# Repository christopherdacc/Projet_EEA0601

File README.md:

# Projet_EEA0601 (Partie IHM)

Programmation en langage C sur MPLAB X IDE d'un microcontrôleur (dsPIC30F4012) pour un système d'IHM d'un robot.
Ce robot a pour fonction de suivre une trajectoire (suit une ligne dessinée par terre), détecter les obstacles et changer de direction pour poursuivre son chemin et une interface IHM pour pouvoir entrer des informations au microcontrôleur avec 3 boutons.

"Séances de travail surveillées et supplémentaires avec tâches réalisées"

* Séance 1 (24/01/2024):
      Explication du projet par les professeurs.
  
* Séance 2 (31/01/2024):
      Branchement d'un afficheur LCD (EA DOGM163W-A) et allumage du rétroéclairage.

* Séance 2.1 sup (02/02/2024):
      programmation et affichage de 'Bonjour le monde!' sur l'écran LCD.
  
* Séance 3 (07/02/2024):
      Branchement des boutons avec leurs résistances spécifiques.

* Séance 4 (14/02/2024):
      Programmation des boutons pour savoir s'ils sont appuyés ou non en affichant leurs états sur l'écran LCD.

* Séance 5 (21/02/2024):
      Rajout des librairies sur Eagle.
      Réalisation du schéma de la carte électronique sur Eagle.

* Séance 5.1 sup (22/02/2024):
      Finalisation du schéma de la carte électronique sur Eagle.
      Début de la réalisation de la carte électronique sur Eagle ainsi que le typon.
* Séance 5.2 sup (23/02/2024):
      Début de la programmation d'un menu avec les options de test des boutons et changement de l'éclairage de l'écran.

* Travail Vacances 6 (du 24/02/2024 au 02/03/2024):
      Finalisation du code menu (prototype)
      Erreur de Build du code.

* Séance 6.1 test du code (05/03/2024):
      Test du code et correction du build error.
      Nouveau probleme code ne marche pas comme on veux.

* Séance 7 (06/03/2024):
      Correction du Schéma de la carte.
      Correction de la carte par rapport au changements du schéma.
      Un peut de modification du code pour qu'il marche (ne marche toujours pas).

* Séance 7.1 sup (07/03/2024):
      Correction de l'affichage du menu (sélection de choix marche bien mais les choix ne marchent pas a 100%)

* Séance 7.2 sup (11/03/2024):
      Correction de la fonction délai.
      Travail sur le compte rendu.

* Séance 8 (13/03/2024):
      On a continué le routage des pistes.
      On a changer les pates des boutons et de l'ecran pour mettre les pates des boutons sur les pates CN qui permettent les interuptions sur front.
  
* Séance 9 (20/03/2024):
      On a finit la carte électronique avec le dimentionnement des pistes de +5V (0.05 inch) et pistes de signaux (0.024).
      On a cassé les angles et tout ca pour evité le rayonnement electromagnetique.

* Séance 10 (27/03/2024):
      On a percé la carte pour pouvoir souder les composants decu.

* Séance 10.1 sup (28/03/2024):
      On a réalisé le test de continuité a l'ohm mètre.
      On a resouder une piste défectueuse.
      On a souder tout les composants sur la carte.
* Séance 11 (03/04/2024):
      Reprogrammation du test des boutons en utilisant des iterruptions.
      Interruptions fonctionnent mais que sur le bouton 3.

* Séance 11.1 sup (09/04/2024):
      Correction du code de l'interruption (Fonctionnement parfait des boutons).
      Essai d'integrer la structure Keyboard avec les objets, mais pas de success.
      Changement du bouton rouge.
      Pendant le test du code, on a rencontrer un probleme de fonctionnement du microcontrolleur.
      Probleme de cablage au niveau de l'alimentation du microcontrolleur.

* Séance 12 (10/04/2024):
      Réglage du probleme de cablage au niveau de l'alimentation du microcontrolleur.
      Le code fonctionne a nouveau.
      Ajout de la fonction menu_principale() pour afficher le menu avec les different choix.
      Programmation de la navigation du curseur pour selectionner 1 des 3 choix avec prog de la saisier du choix 1 (Actions).
* Pour la prochaine séance :        - Essayer de remplacer les statusB, statusN et statusR par la structure keyboard.
                                    - Implémanter cette structure dans la fonction menu_principale().
                                    - Continuer la programmation de l'affichage.
  
* Séance 12.1 sup (13/04/2024):
      On a realiser les taches pécedantes (remplacement statusB.../implementer la struct keyboard.../ continuer la programmation de l'affichage).
      On a essayer d'implémenter les strcutures Menu, MenuItem et MenuValue mais on a pas réussi.

* Séance 12.2 sup (16/04/2024):
      On a continuer l'affichage du menu et differente options du menu avec des if et else if.
      On a réessayer d'implenter les structures Menu, MenuItem et MenuValue maus on a toujours pas réussi.
      On a essayer d'ajouter le keybord->upstate=2 pour une appuie de 2s sur le bouton rouger, mais on a pas réussi.

* To do: try using macros to simplify and reduce memory usage.

* Séance 13 (17/04/2024):
      On a utiliser macros (#define) pour l'operation moyenne%3
      On pu utiliser ticks.c pour pouvoir determiner l'appui de 2s sur un bouton.
      On a continuer la partie parametres->reglage detection obs pour essayer d'afficher un chiffre et l'incrémenter mais l'addition de chiffre et considere comme un char.
      On a vite fait compris le fonctionnement des differentes struct du menu(Menu, MenuItem et MenuValue) et l'utilisation d'une array pour stocker les differents MenuItems.

* To do: implementer les 3 structures du menu a la fonction menu_principale, réessayer la configuration de l'affichage d'un int modifiable sur l'ecran,

* Séance 13.1 sup (19/04/2024):
      On a réussi a configurer l'affichage d'un int qu'on peut incrémenter et décrémenter a l'aide des boutons pour la partie Parametres->Detection obstacle.
  
* Séance 14 (07/05/2024):
      On a finaliser le menu (partie affichage et manupulation du menu).
      Il nous reste la partie parametre (PID et vitesse) a réglé.
      Il nous reste les interruption pour recevoir et transmettre les info des capteurs et moteurs.
      il nous reste a configurer la structure MenuValues pour pouvoir envoyer les parametres au moteur.

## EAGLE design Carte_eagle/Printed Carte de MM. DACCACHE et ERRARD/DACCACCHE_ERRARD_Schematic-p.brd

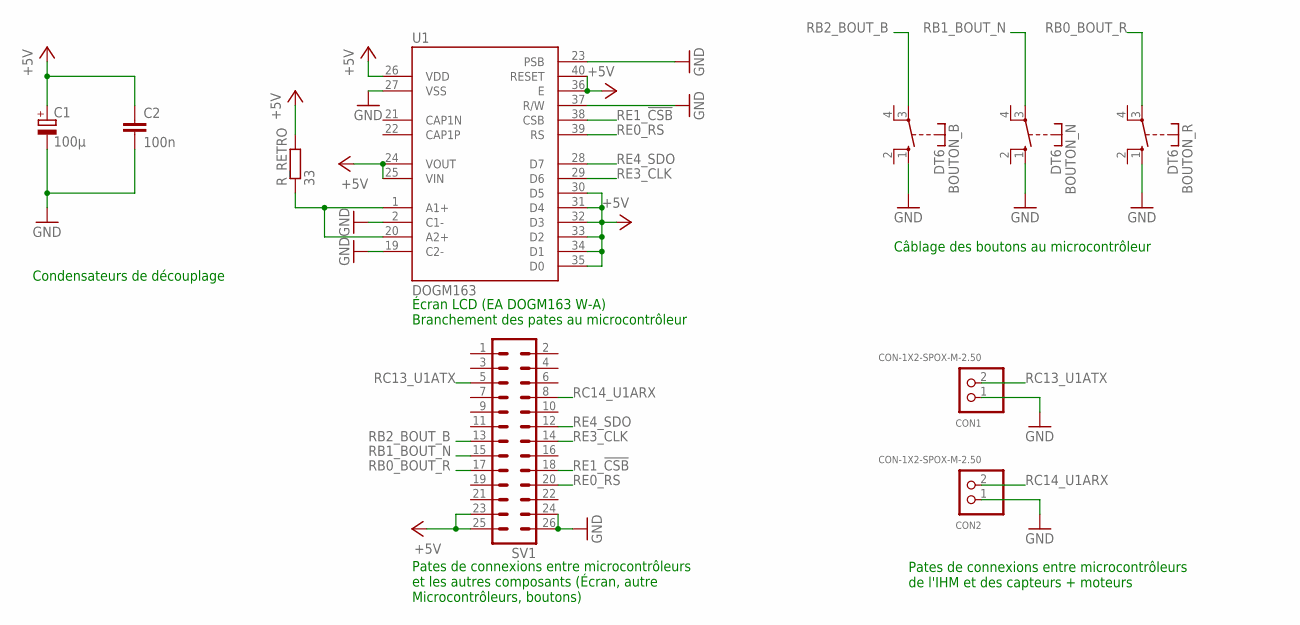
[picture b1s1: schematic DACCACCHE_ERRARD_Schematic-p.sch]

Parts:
BOUTON_B: DT6
BOUTON_N: DT6
BOUTON_R: DT6
C1: 100µ; E2,5-7
C2: 100n; C050-030X075
CON1, CON2: CON-1X2-SPOX-M-2.50; SPOX-M-2.50-02
R_RETRO: 33; 0207/10
SV1: ML26
U1: DOGM163; DOGM

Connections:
+5V: C1.+, C2.1, R_RETRO.2, SV1.23, SV1.25, U1.24 (VOUT), U1.25 (VIN), U1.26 (VDD), U1.30 (D5), U1.31 (D4), U1.32 (D3), U1.33 (D2), U1.34 (D1), U1.35 (D0), U1.36 (E), U1.40 (RESET)
GND: BOUTON_B.1 (S), BOUTON_N.1 (S), BOUTON_R.1 (S), C1.-, C2.2, CON1.1, CON2.1, SV1.24, SV1.26, U1.2 (C1-), U1.19 (C2-), U1.23 (PSB), U1.27 (VSS), U1.37 (R/W)
RB0_BOUT_R: BOUTON_R.3, SV1.17
RB1_BOUT_N: BOUTON_N.3, SV1.15
RB2_BOUT_B: BOUTON_B.3, SV1.13
RC13_U1ATX: CON1.2, SV1.5
RC14_U1ARX: CON2.2, SV1.8
RE0_RS: SV1.20, U1.39 (RS)
RE1_!CSB: SV1.18, U1.38 (CSB)
RE3_CLK: SV1.14, U1.29 (D6)
RE4_SDO: SV1.12, U1.28 (D7)
RHETRO_RES: R_RETRO.1, U1.1 (A1+), U1.20 (A2+)

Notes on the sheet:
Écran LCD (EA DOGM163 W-A) Branchement des pates au microcontrôleur
Câblage des boutons au microcontrôleur
Pates de connexions entre microcontrôleurs de l'IHM et des capteurs + moteurs
Pates de connexions entre microcontrôleurs et les autres composants (Écran, autre Microcontrôleurs, boutons)
Condensateurs de découplage

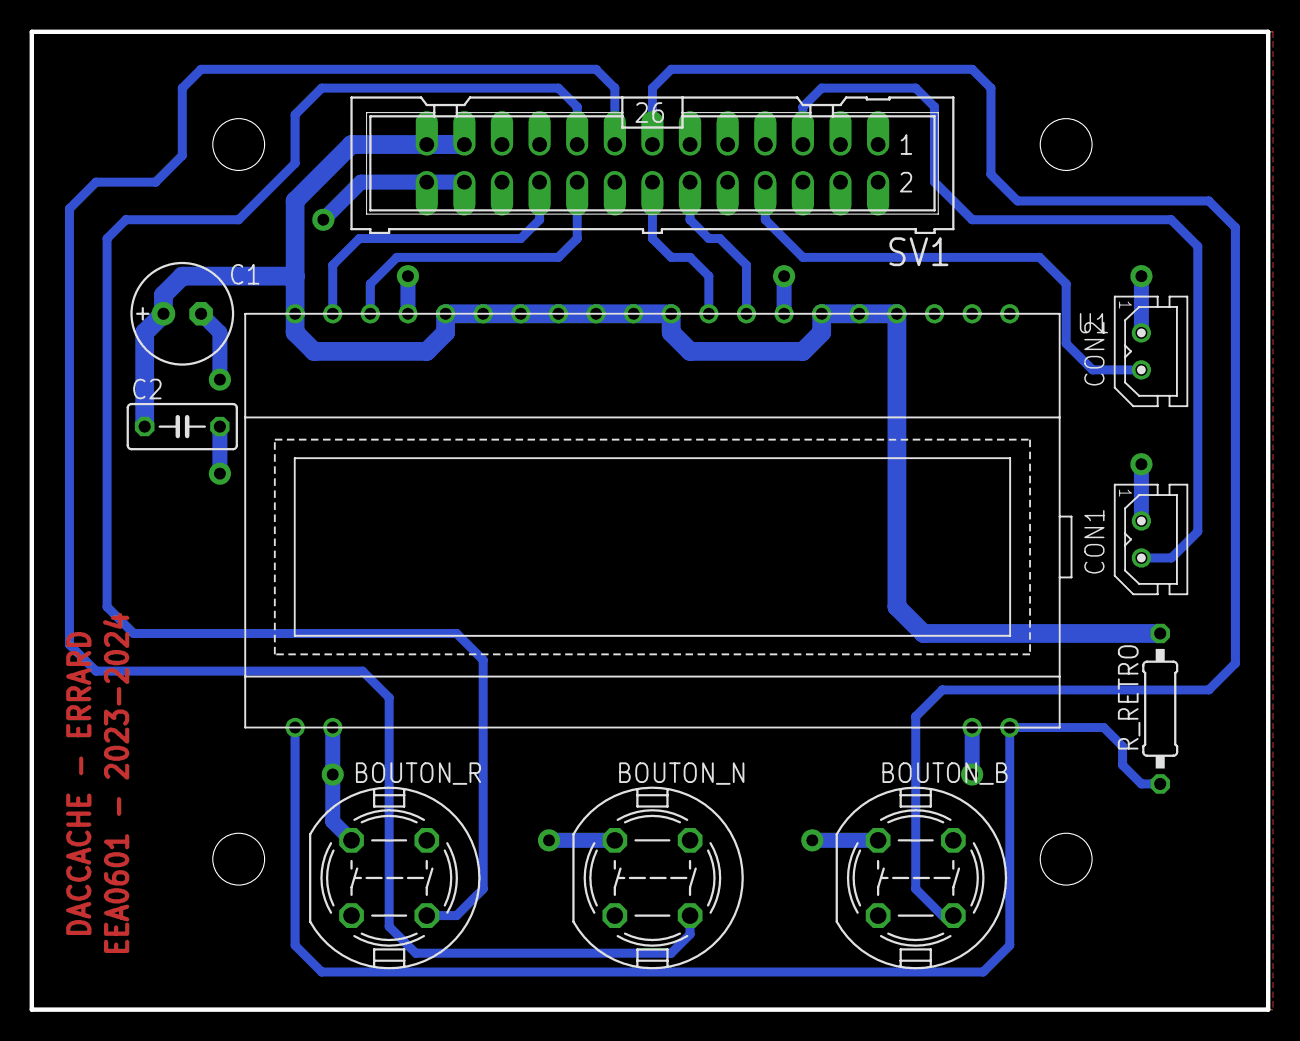
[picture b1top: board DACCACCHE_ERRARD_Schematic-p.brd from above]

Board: 2 copper layers, 83.5 x 66.0 mm, 10 parts (0 on the bottom side), 12 nets.

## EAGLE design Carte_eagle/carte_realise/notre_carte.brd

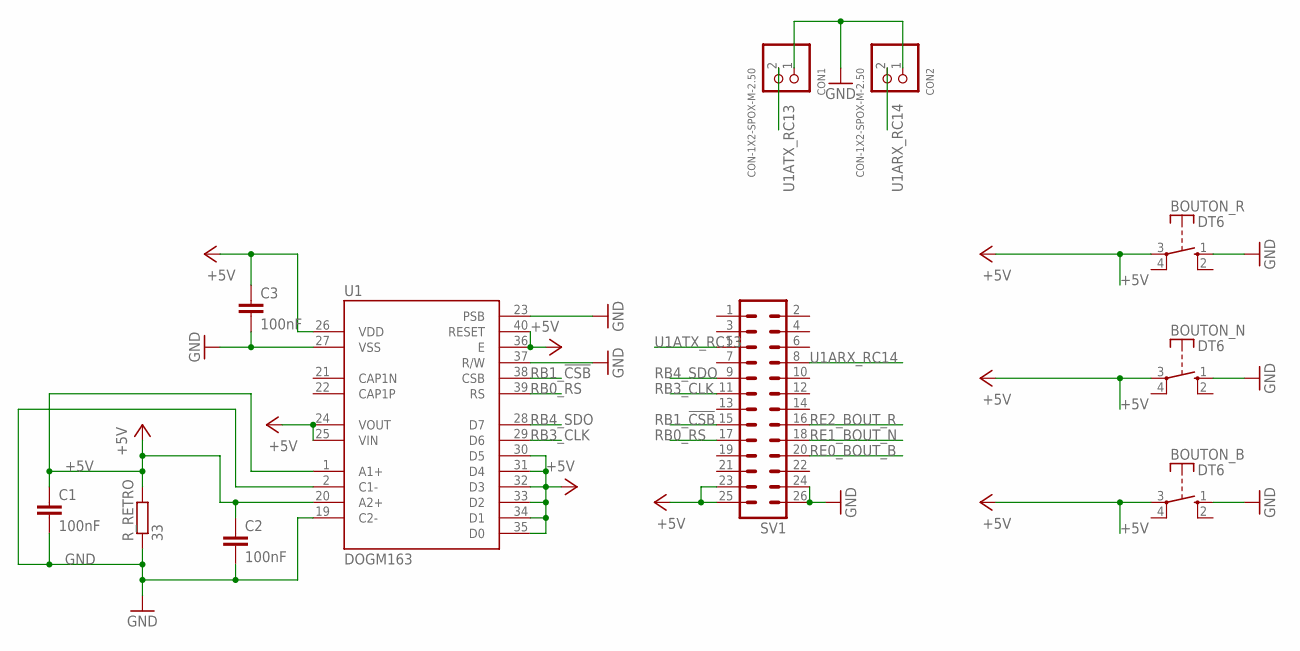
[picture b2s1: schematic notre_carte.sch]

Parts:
BOUTON_B: DT6
BOUTON_N: DT6
BOUTON_R: DT6
C1, C2, C3: 100nF; C025-025X050
CON1, CON2: CON-1X2-SPOX-M-2.50; SPOX-M-2.50-02
R_RETRO: 33; 0207/15
SV1: ML26
U1: DOGM163; DOGM

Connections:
+5V: BOUTON_B.3, BOUTON_N.3, BOUTON_R.3, C1.1, C2.1, C3.1, R_RETRO.2, SV1.23, SV1.25, U1.1 (A1+), U1.20 (A2+), U1.24 (VOUT), U1.25 (VIN), U1.26 (VDD), U1.30 (D5), U1.31 (D4), U1.32 (D3), U1.33 (D2), U1.34 (D1), U1.35 (D0), U1.36 (E), U1.40 (RESET)
GND: BOUTON_B.1 (S), BOUTON_N.1 (S), BOUTON_R.1 (S), C1.2, C2.2, C3.2, CON1.1, CON2.1, R_RETRO.1, SV1.24, SV1.26, U1.2 (C1-), U1.19 (C2-), U1.23 (PSB), U1.27 (VSS), U1.37 (R/W)
RB0_RS: SV1.17, U1.39 (RS)
RB1_!CSB: SV1.15, U1.38 (CSB)
RB3_CLK: SV1.11, U1.29 (D6)
RB4_SDO: SV1.9, U1.28 (D7)
RE0_BOUT_B: SV1.20
RE1_BOUT_N: SV1.18
RE2_BOUT_R: SV1.16
U1ARX_RC14: CON2.2, SV1.8
U1ATX_RC13: CON1.2, SV1.5

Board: 2 copper layers, 11 parts (0 on the bottom side), 8 nets, no tracks yet.

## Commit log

2024-02-21 Create README.md
    Add a new README.md file
2024-02-21 Update README.md
    Update README.md
2024-02-21 Upload Eagle Schematics
    Upload of first eagle schematics: lcd connections, buttons, microcontroller conections using 26 pins connector ML26, pins for other microcontroller connections.
2024-02-21 Upload of Schematics Screenshot
2024-02-21 Update carte elec
2024-02-22 Updated schematics of the board
    mise a jour du schéma de la carte électronique réalisé sur eagle, (addition des capacités de découplage de 100nF et amélioration des connections de fils)
2024-02-22 Delete Carte_eagle/carte_realise/carte_realise directory
    faute d'addition
2024-02-23 Programming changes
    Adding menu function
2024-02-26 Update README.md
    update séance du vendredi 23
2024-03-01 mise a jour du code main.c
    finalisation de la fonction menu dans les fichiers a rajouter apres (fonctions_sup.h et fonctions_sup.c)
2024-03-01 Mise a jour de fonctions_sup.h et fonctions_sup.c
    Finalisation de la fonction du menu (prototype) a essayer en classe
2024-03-06 Update file main.c
    Mise du code dans le fichié fonctions_sup.c
2024-03-06 Modification de fonctions.h et fonctions.c
2024-03-06 mise a jour de la carte et board
2024-03-06 Rename DACCACCHE_ERRARD_Schematic.sch.xml to DACCACCHE_ERRARD_Schematic.sch
    Changement d'extension
2024-03-06 new board and schematics
2024-03-07 Reparation du menu fichier fonction_sup.c
    le menu maintenant affiche les choix et on peux bien sélectionner un choix, mais il y a un peut de retard (a rajouter une fonction wait).
    Après avoir sélectionner un choix c'est le bazar (a réparé)
2024-03-11 upload files to compte rendu
2024-03-11 Upload pictures de code et carte elec
2024-03-11 Upload compte rendu
    Quelques modifications et rajout de la partie programmation
2024-03-11 Modification de schematics eagle
    Rajout des commentaires sur le schéma
2024-03-12 upload compte rendu EEA0601 derniere version
2024-03-13 upload compte rendu pdf and pics
2024-03-20 update board et schematics
    finalisation du schema avec le changement des pins de l'ecran et des boutons
    finalisation de la carte avec l'epaisseur des cables et le cassage des angles droits
2024-03-27 Upload carte imprimé
    Upload des fichiers imprimé par monsieur Brasseur (carte.brd, carte.sch, top.pdf et bot.pdf)
2024-04-03 update code
    add interruption for CN pins and the functions of initialisation et eneble interrupt
2024-04-09 Update main.c
    correction des pullups (etats des boutons + initerruption)
2024-04-10 update modelX
    add function menu
    correction interruption buttons
    add struct
2024-04-12 Update main.c function_suo.h and .c
    utilisation du struct keyboard au lieu des stateR, stateN et stateB
    ajout d'un retour en arriere pour la fonction menu_principale
2024-04-16 update modele.X
    added more menue selection
2024-04-16 Update README.md
    test
2024-04-17 update modele.X
    changements dand readme de cette seance
2024-04-17 new test.x
    testing code
2024-04-19 Update model.X
    On a reussi a incrementer une variable int et l'afficher en meme temps pour la partie distance obstacle dans parametres.
2024-05-06 update fonctions_sup.c et .h
    ajout des structure menu, menuitems et menuvalues
    programmation d'une part du menu avec ces strucutres
2024-05-07 update fonctions_sup.c et .h
    finialisation de la programmation du menu avec les structure
    il nous reste a faire dans la partie parametre (reglage pid et vitesse)
2024-05-14 upload board pic
2024-05-14 Add files via upload
    Photo de la carte après soudure
2024-05-15 update compte rendu
2024-05-15 update compte rendu 2
